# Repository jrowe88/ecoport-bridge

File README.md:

# EcoPort Bridge

EcoPort Bridge is a hobby reverse-engineering and hardware project to build a
communication bridge for appliances using the **CTA-2045 "EcoPort"** interface
(AC-form-factor UCM connector, RS-485 @ 19,200 baud) — starting with a
**Rinnai REHP65** heat pump water heater (CTA-2045-B / SGD, connector CN50,
physical connector part `420B2V12FL0`).

The goal is to expose the appliance's CTA-2045 data (tank temperature,
setpoint, operating state, energy, demand-response/shed status, faults, etc.)
to home automation systems (MQTT, Matter, Home Assistant) via a small
ESP32-class bridge device, built on top of a Python implementation of the
CTA-2045 protocol.

*Rev A: ESP32-C6 board with an on-board mains supply, plugged straight into
the heater's CTA-2045 connector. See [`hardware/rev-a`](hardware/rev-a) for
the board and [`hardware/enclosure`](hardware/enclosure) for the 3D-printed
case.*

## Design principles

- **Generic CTA-2045 core, separate from appliance-specific logic.** The
  `cta2045` layer implements the protocol (framing, messages, CRC, link,
  Basic DR / Intermediate messages). Appliance-specific behavior (e.g. Rinnai
  REHP65 quirks and capability mappings) lives under `appliances/rinnai` (or
  a Rinnai crate in firmware) so other CTA-2045/EcoPort appliances can be
  supported later without untangling Rinnai assumptions from the protocol
  implementation.
- **Protocol reverse engineering is kept separate from electrical reverse
  engineering.** Most of the protocol can be worked out via the EPRI UCM
  simulator without ever touching the heater.
- **Facts vs. hypotheses are recorded separately** in `docs/protocol.md` and
  per-capture notes, so reverse-engineering guesses don't quietly turn into
  "the spec" later.
- **Captures are first-class project artifacts.** Raw captures + notes live
  under `captures/` as a reproducible dataset, not a pile of Wireshark
  screenshots.

## Architecture

```text
                   ┌───────────────────────────────┐
                   │       Your application        │
                   │ Home Assistant / MQTT / etc.  │
                   └───────────────┬───────────────┘
                                   │
                         Python CTA-2045 API
                                   │
                   ┌───────────────▼───────────────┐
                   │       CTA-2045 protocol       │
                   │ link + Basic DR + Intermediate│
                   └───────────────┬───────────────┘
                                   │
                              RS-485 UART
                                   │
                   ┌───────────────▼───────────────┐
                   │       Isolated RS-485         │
                   │       transceiver             │
                   └───────────────┬───────────────┘
                                   │
                         CTA-2045 AC connector
                                   │
                   ┌───────────────▼───────────────┐
                   │       Rinnai REHP65           │
                   │          SGD / CN50           │
                   └───────────────────────────────┘
```

## Hardware notes (confirmed)

- Physical connector: `420B2V12FL0` (EPRI's "UCM Connector")
- Only pins **1 (D-), 7 (D+), 8 (GND)** are used; all other pins are left
  unconnected.
- EPRI documents 19,200 baud, 8 data bits, 1 stop bit, no parity.
- This is a mains-adjacent AC-form-factor interface — treat it with a
  deliberate electrical isolation strategy (isolated USB/RS-485 adapter).

See `docs/hardware.md` and `docs/protocol.md` for details, and `captures/`
for recorded traffic.

## Repository layout

```text
ecoport-bridge/
│
├── README.md
├── LICENSE             # AGPL-3.0 (software); hardware/LICENSE is CERN-OHL-S-2.0
├── CONTRIBUTING.md
│
├── docs/                 # architecture, hardware, protocol, HOWTOs
├── hardware/             # PCB revisions + 3D-printed enclosure
├── firmware/             # ESP32-C6 bridge firmware (Rust on ESP-IDF)
├── python/               # ecoport Python package (protocol + tooling)
├── tools/                # CLI tools: sniff, decode, query, interactive
├── captures/             # recorded protocol traffic + notes (EPRI + Rinnai)
├── test/                 # cross-cutting test fixtures/integration tests
└── scripts/              # dev setup / flashing helpers
```

## Status

Early planning / hardware on order. See `docs/reverse-engineering.md` and
`captures/` as the project progresses.

## Documentation

- [`docs/architecture.md`](docs/architecture.md) — software layering and the device ↔ Azure cloud architecture (telemetry, commands, storage, dashboard, security)
- [`docs/hardware.md`](docs/hardware.md) — connector, pinout, safety, bring-up hardware
- [`docs/protocol.md`](docs/protocol.md) — CTA-2045 protocol facts, capability matrix
- [`docs/capabilities.md`](docs/capabilities.md) — what we can see, infer, log and control on the Rinnai REHP65
- [`docs/reverse-engineering.md`](docs/reverse-engineering.md) — staged plan (EPRI oracle → passive capture → queries → writes)
- [`docs/references.md`](docs/references.md) — source material, tools, and libraries (EPRI, `python-cta2045`, ANSI, EcoPort DB, OpenADR, connector part numbers)
- [`docs/troubleshooting.md`](docs/troubleshooting.md) — common issues

## License

Both licenses are copyleft: you can use, modify and share this project, and
anything you distribute that's based on it has to stay under the same terms.

- **Software** (`firmware/`, `python/`, `tools/`, `scripts/`, `test/`) —
  GNU Affero General Public License v3.0 (`AGPL-3.0-only`), see
  [LICENSE](LICENSE).
- **Hardware** (`hardware/`: KiCad board, footprints, fab outputs, enclosure
  CAD) — CERN Open Hardware Licence v2, Strongly Reciprocal
  (`CERN-OHL-S-2.0`), see [hardware/LICENSE](hardware/LICENSE).
- **Docs and captures** — AGPL-3.0, same as the software.

Source location for the hardware (CERN-OHL-S §1.9):
<https://github.com/jrowe88/ecoport-bridge>. It is also printed on the board.

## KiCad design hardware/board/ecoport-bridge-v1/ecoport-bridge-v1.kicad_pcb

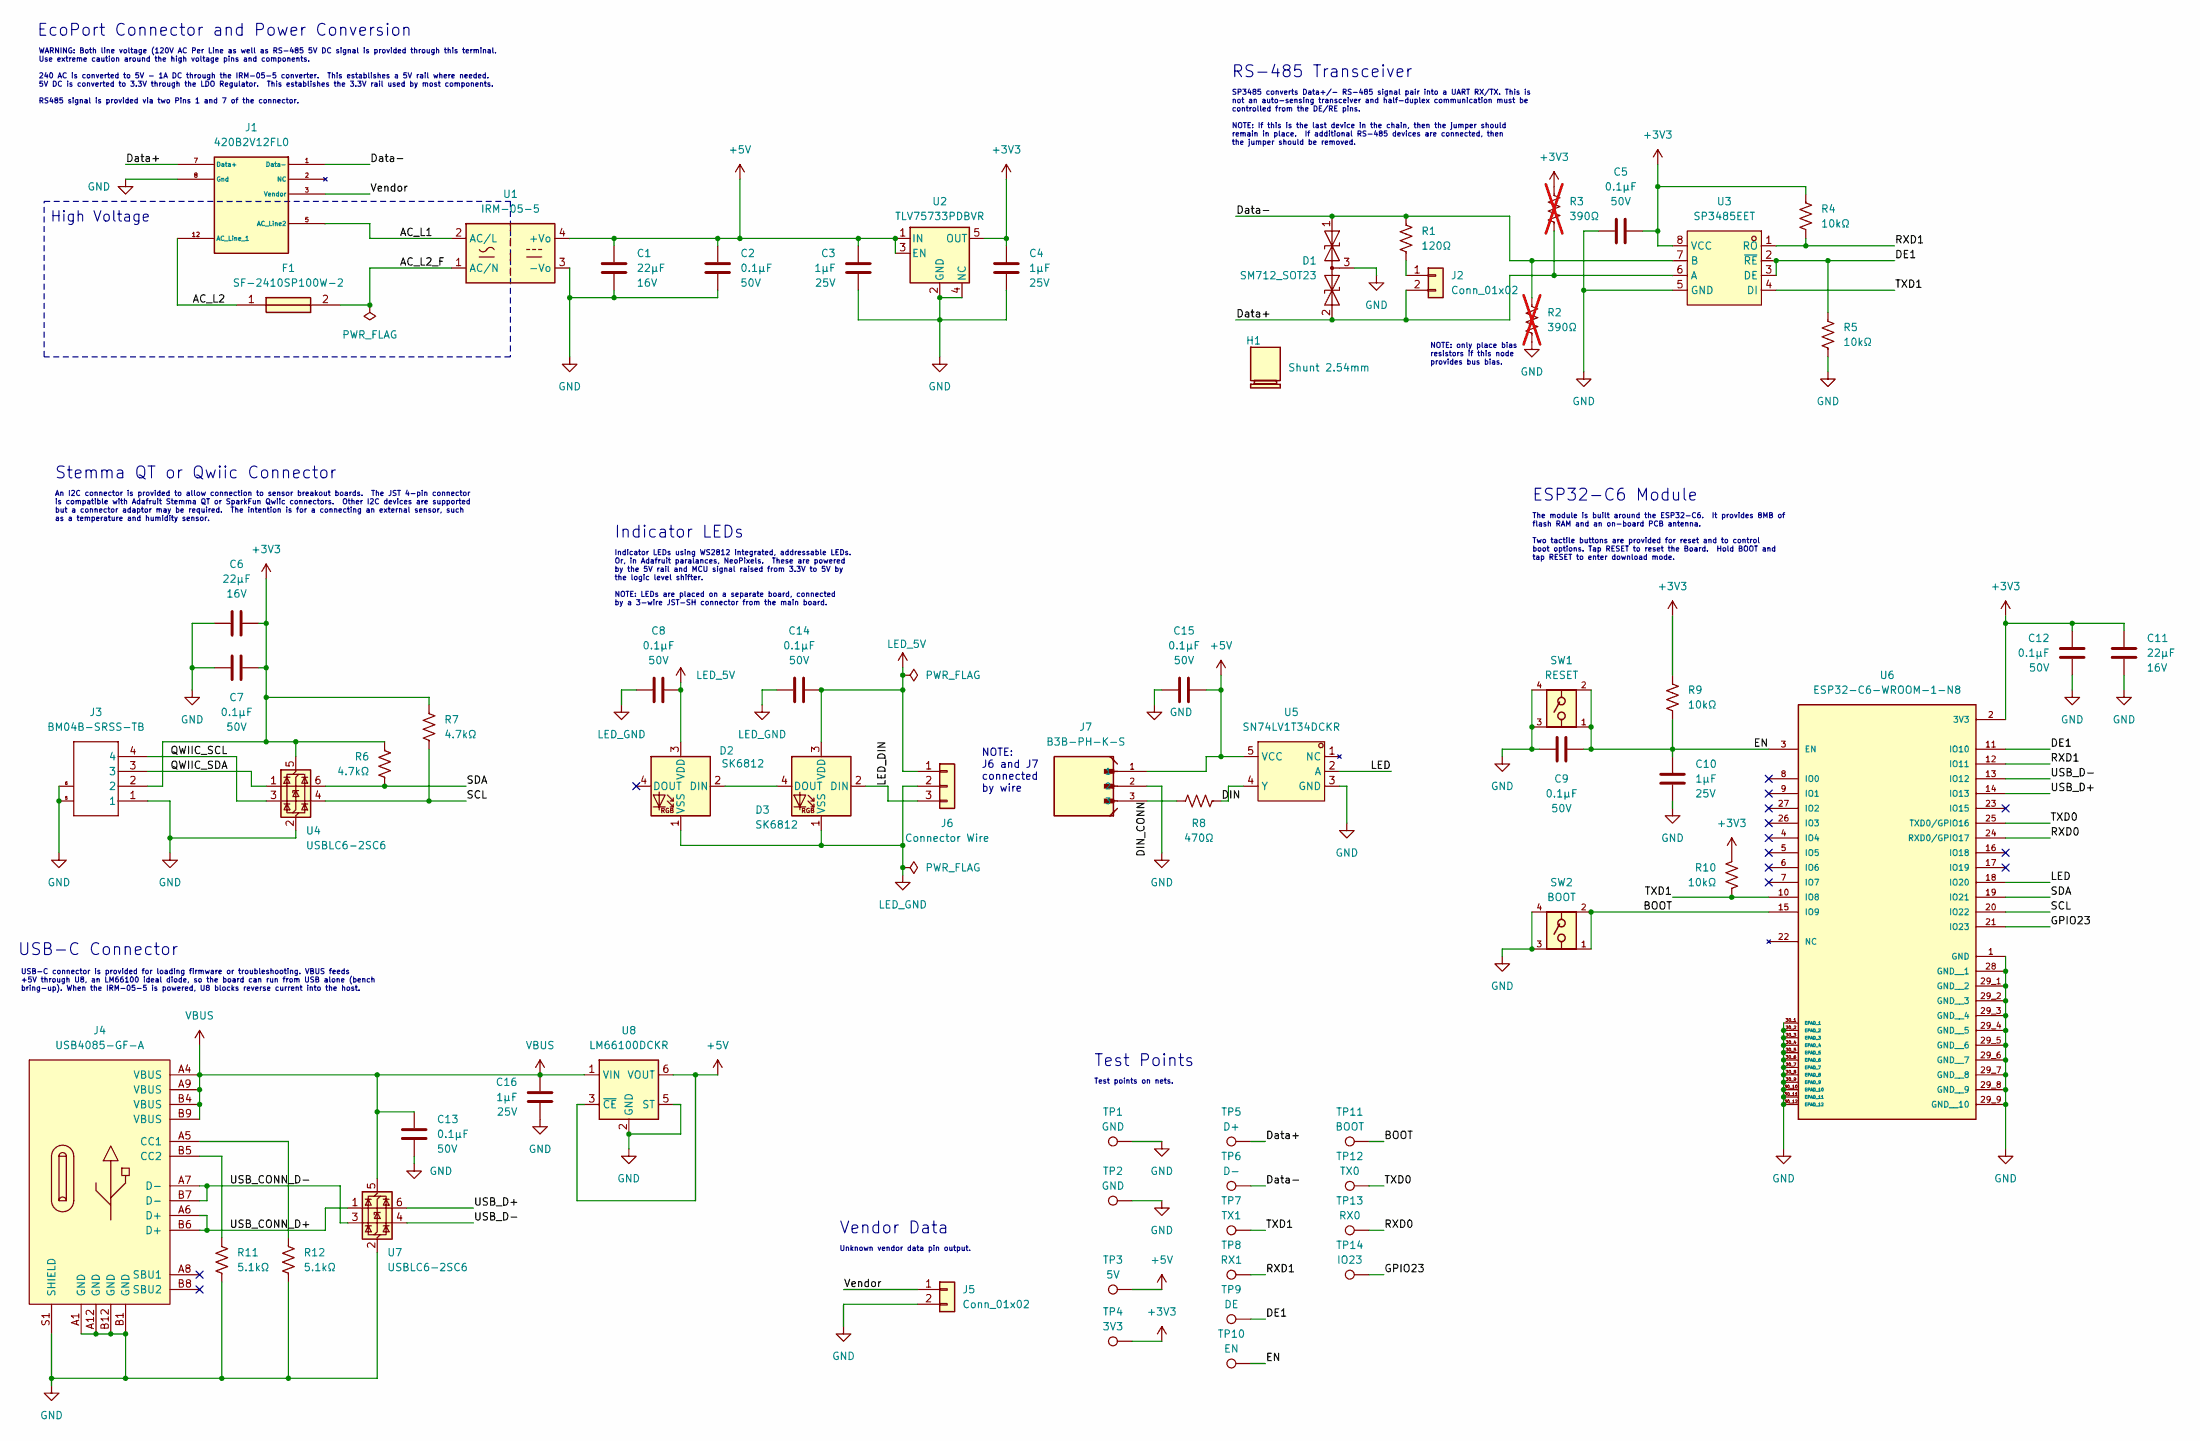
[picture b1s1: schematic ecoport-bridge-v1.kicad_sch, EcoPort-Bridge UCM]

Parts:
C1, C6, C11: 22µF; C_1206_3216Metric; Voltage 16V; MPN GRM319R61C226ME15J
C2, C5, C7, C8, C9, C12, C13, C14, C15: 0.1µF; C_0603_1608Metric; Voltage 50V; MPN GCJ188R71H104KA12D
C3, C4, C10, C16: 1µF; C_0603_1608Metric; Voltage 25V; MPN GRT188R71E105KE13D
D1: SM712_SOT23; SOT-23; MPN SM712
D2, D3: SK6812; LED_SK6812_PLCC4_5.0x5.0mm_P3.2mm; MPN SK6812
F1: SF-2410SP100W-2; FUSC6125X236N; Manufacturer_Part_Number SF-2410SP100W-2; Mouser Part Number 652-SF-2410SP100W-2
H1: Shunt 2.54mm; MPN QPC02SXGN-RC
J1: 420B2V12FL0; Onshore_Header_2x06_P4.20mm_Vertical; MPN 420B2V12FL0
J2, J5: Conn_01x02; PinHeader_1x02_P2.54mm_Vertical; MPN PREC002SAAN-RC
J3: BM04B-SRSS-TB; CONN4_BM04B-SRSS_JST; MPN BM04B-SRSS-TB(LF)(SN)
J4: USB4085-GF-A; USC-C-SMD_USB4085-GF-A; MPN USB4085-GF-A; LCSC Part C9900013983
J6: Connector Wire; Wire_Solder_1x03_P2.54mm_Relief
J7: B3B-PH-K-S; JST_B3B-PH-K-S; MPN B3B-PH-K-S(LF)(SN)
R1: 120Ω; R_1206_3216Metric; MPN RC1206FR-07120RL
R2, R3: 390Ω; R_0603_1608Metric; MPN RC0603FR-07390RL; not fitted
R4, R5, R9, R10: 10kΩ; R_0603_1608Metric; MPN RC0603FR-0710KL
R6, R7: 4.7kΩ; R_0603_1608Metric; MPN RC0603FR-074K7L
R8: 470Ω; R_0603_1608Metric; MPN RC0603FR-07470RL
R11, R12: 5.1kΩ; R_0603_1608Metric; MPN RC0603FR-075K1L
SW1: RESET; SW_TS04-66-50-BK-260-SMT; PARTREV 1.0
SW2: BOOT; SW_TS04-66-50-BK-260-SMT; PARTREV 1.0
TP1, TP2: GND; TestPoint_Keystone_5000-5004_Miniature; MPN 5001
TP3: 5V; TestPoint_Keystone_5000-5004_Miniature; MPN 5000
TP4: 3V3; TestPoint_Keystone_5000-5004_Miniature; MPN 5000
TP5: D+; TestPoint_Pad_D2.0mm
TP6: D-; TestPoint_Pad_D2.0mm
TP7: TX1; TestPoint_Pad_D2.0mm
TP8: RX1; TestPoint_Pad_D2.0mm
TP9: DE; TestPoint_Pad_D2.0mm
TP10: EN; TestPoint_Pad_D2.0mm
TP11: BOOT; TestPoint_Pad_D2.0mm
TP12: TX0; TestPoint_Pad_D2.0mm
TP13: RX0; TestPoint_Pad_D2.0mm
TP14: IO23; TestPoint_Keystone_5000-5004_Miniature; MPN 5000
U1: IRM-05-5; Converter_ACDC_MeanWell_IRM-05-xx_THT; MPN IRM-05-5
U2: TLV75733PDBVR; SOT-23-5; MPN TLV75733PDBVR
U3: SP3485EET; TSSOP-8_L4.4-W3.0-P0.65-LS6.4-BL; MPN SP3485EET; LCSC Part C20617894
U4, U7: USBLC6-2SC6; SOT-23-6; MPN USBLC6-2SC6
U5: SN74LV1T34DCKR; SC-70-5_L2.1-W1.3-P0.65-LS2.1-BR; MPN SN74LV1T34DCKR; LCSC Part C78541
U6: ESP32-C6-WROOM-1-N8; XCVR_ESP32-C6-WROOM-1-N8; PARTREV 1.0
U8: LM66100DCKR; SOT-363_SC-70-6; MPN LM66100DCKR

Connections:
+3V3: C4.1, C5.2, C6.2, C7.2, C11.2, C12.2, J3.2, R3.2, R4.2, R6.1, R7.1, R9.2, R10.2, TP4.1 (1_1), U2.5 (OUT), U3.8 (VCC), U4.5 (VBUS), U6.2 (3V3)
+5V: C1.1, C2.1, C3.1, C15.2, J7.1, TP3.1 (1_1), U1.4 (+Vo), U2.1 (IN), U2.3 (EN), U5.5 (VCC), U8.3 (~CE), U8.6 (VOUT)
/AC_L1: J1.5 (AC_Line2), U1.2 (AC/L)
/AC_L2: F1.1, J1.12 (AC_Line_1)
/AC_L2_F: F1.2, U1.1 (AC/N)
/BOOT: SW2.1, SW2.2, TP11.1 (1_1), U6.15 (IO9)
/DE1: R5.2, TP9.1 (1_1), U3.2 (~RE), U3.3 (DE), U6.11 (IO10)
/DIN: R8.1, U5.4 (Y)
/DIN_CONN: J7.3, R8.2
/Data+: D1.2 (A2), J1.7 (Data+), J2.2, R3.1, TP5.1 (1_1), U3.6 (A)
/Data-: D1.1 (A1), J1.1 (Data-), R1.1, R2.2, TP6.1 (1_1), U3.7 (B)
/EN: C9.2, C10.1, R9.1, SW1.1, SW1.2, TP10.1 (1_1), U6.3 (EN)
/GPIO23: TP14.1 (1_1), U6.21 (IO23)
/LED: U5.2 (A), U6.18 (IO20)
/LED_DIN: D3.2 (DIN), J6.3
/QWIIC_SCL: J3.4, U4.3 (I/O2)
/QWIIC_SDA: J3.3, U4.1 (I/O1)
/RXD0: TP13.1 (1_1), U6.24 (RXD0/GPIO17)
/RXD1: R4.1, TP8.1 (1_1), U3.1 (RO), U6.12 (IO11)
/SCL: R7.2, U4.4 (I/O2), U6.20 (IO22)
/SDA: R6.2, U4.6 (I/O1), U6.19 (IO21)
/TXD0: TP12.1 (1_1), U6.25 (TXD0/GPIO16)
/TXD1: R10.1, TP7.1 (1_1), U3.4 (DI), U6.10 (IO8)
/USB_CONN_D+: J4.A6 (D+), J4.B6 (D+), U7.1 (I/O1)
/USB_CONN_D-: J4.A7 (D-), J4.B7 (D-), U7.3 (I/O2)
/USB_D+: U6.14 (IO13), U7.6 (I/O1)
/USB_D-: U6.13 (IO12), U7.4 (I/O2)
/Vendor: J1.3 (Vendor), J5.1
GND: C1.2, C2.2, C3.2, C4.2, C5.1, C6.1, C7.1, C9.1, C10.2, C11.1, C12.1, C13.1, C15.1, C16.2, D1.3 (common), J1.8 (Gnd), J3.1, J3.5, J3.6, J4.A1 (GND), J4.A12 (GND), J4.B1 (GND), J4.B12 (GND), J4.S1 (SHIELD), J5.2, J7.2, R2.1, R5.1, R11.1, R12.1, SW1.3, SW1.4, SW2.3, SW2.4, TP1.1 (1_1), TP2.1 (1_1), U1.3 (-Vo), U2.2 (GND), U2.4 (NC), U3.5 (GND), U4.2 (GND), U5.3 (GND), U6.1 (GND), U6.28 (GND__1), U6.29_1 (GND__2), U6.29_2 (GND__3), U6.29_3 (GND__4), U6.29_4 (GND__5), U6.29_5 (GND__6), U6.29_6 (GND__7), U6.29_7 (GND__8), U6.29_8 (GND__9), U6.29_9 (GND__10), U6.30_1 (EPAD_1), U6.30_2 (EPAD_2), U6.30_3 (EPAD_3), U6.30_4 (EPAD_4), U6.30_5 (EPAD_5), U6.30_6 (EPAD_6), U6.30_7 (EPAD_7), U6.30_8 (EPAD_8), U6.30_9 (EPAD_9), U6.30_10 (EPAD_10), U6.30_11 (EPAD_11), U6.30_12 (EPAD_12), U7.2 (GND), U8.2 (GND), U8.5 (ST)
LED_5V: C8.2, C14.2, D2.3 (VDD), D3.3 (VDD), J6.1
LED_GND: C8.1, C14.1, D2.1 (VSS), D3.1 (VSS), J6.2
unnamed: D2.2 (DIN), D3.4 (DOUT)
unnamed: J2.1, R1.2
unnamed: J4.A5 (CC1), R12.2
unnamed: J4.B5 (CC2), R11.2
VBUS: C13.2, C16.1, J4.A4 (VBUS), J4.A9 (VBUS), J4.B4 (VBUS), J4.B9 (VBUS), U7.5 (VBUS), U8.1 (VIN)

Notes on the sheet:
Stemma QT or Qwiic Connector
Indicator LEDs
ESP32-C6 Module
WARNING: Both line voltage (120V AC Per Line as well as RS-485 5V DC signal is provided through this terminal. Use extreme caution around the high voltage pins and components. 240 AC is converted to 5V - 1A DC through the IRM-05-5 converter. This establishes a 5V rail where needed. 5V DC is convert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
NOTE: J6 and J7 connected by wire
EcoPort Connector and Power Conversion
High Voltage
An I2C connector is provided to allow connection to sensor breakout boards. The JST 4-pin connector is compatible with Adafruit Stemma QT or SparkFun Qwiic connectors. Other I2C devices are supported but a connector adaptor may be required. The intention is for a connecting an external sensor, such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
The module is built around the ESP32-C6. It provides 8MB of flash RAM and an on-board PCB antenna. Two tactile buttons are provided for reset and to control boot options. Tap RESET to reset the Board. Hold BOOT and tap RESET to enter download mode.
RS-485 Transceiver
Unknown vendor data pin output.
Test Points
USB-C Connector
SP3485 converts Data+/- RS-485 signal pair into a UART RX/TX. This is not an auto-sensing transceiver and half-duplex communication must be controlled from the DE/RE pins. NOTE: If this is the last device in the chain, then the jumper should remain in place. If additional RS-485 devices are connect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
NOTE: only place bias resistors if this node provides bus bias.
Vendor Data
Indicator LEDs using WS2812 integrated, addressable LEDs. Or, in Adafruit paralances, NeoPixels. These are powered by the 5V rail and MCU signal raised from 3.3V to 5V by the logic level shifter. NOTE: LEDs are placed on a separate board, connected by a 3-wire JST-SH connector from the main board.
USB-C connector is provided for loading firmware or troubleshooting. VBUS feeds +5V through U8, an LM66100 ideal diode, so the board can run from USB alone (bench bring-up). When the IRM-05-5 is powered, U8 blocks reverse current into the host.
Test points on nets.

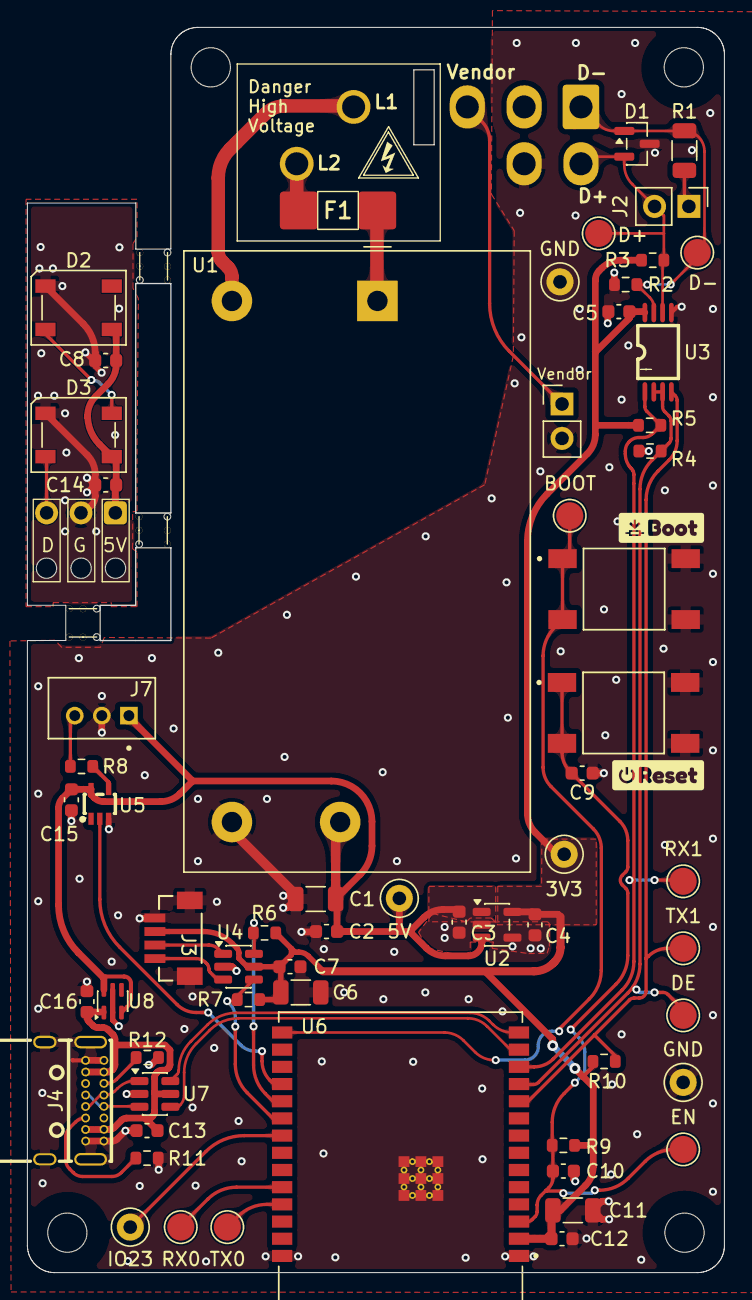
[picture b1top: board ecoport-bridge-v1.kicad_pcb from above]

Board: 2 copper layers, 51.5 x 92.0 mm, 65 parts (1 on the bottom side), 36 nets.

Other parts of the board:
kobee-studio-6AD3D2C7: Kobee Studio; kobee-studio-6AD3D2C7
kobee-studio-6AD3E735: Kobee Studio; kobee-studio-6AD3E735

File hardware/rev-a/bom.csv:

Reference,Description,Manufacturer,MPN,Quantity,DigiKey,Notes
"C1,C6,C11",Cap 22uF 16V X5R 1206,Murata Electronics,GRM319R61C226ME15J,3,490-GRM319R61C226ME15JCT-ND,
"C2,C5,C7,C8,C9,C12-C15",Cap 0.1uF 50V X7R 0603,Murata Electronics,GCJ188R71H104KA12D,9,490-5798-1-ND,
"C3,C4,C10,C16",Cap 1uF 25V X7R 0603,Murata Electronics,GRT188R71E105KE13D,4,490-GRT188R71E105KE13DCT-ND,
D1,TVS RS-485 SM712 SOT-23,SMC Diode Solutions,SM712,1,1655-SM712CT-ND,
"D2,D3",SK6812 addressable LED 5050 PLCC4 (LED strip),OPSCO Optoelectronics,SK6812,2,,Not stocked bare at DigiKey; use own stock or LCSC/Adafruit
F1,Fuse 1A 250VAC time-lag 2410,Bourns,SF-2410SP100W-2,1,SF-2410SP100W-2CT-ND,Marking letter E
H1,Jumper shunt 2.54mm,Sullins Connector Solutions,QPC02SXGN-RC,1,S9337-ND,Termination jumper on J2
J1,CTA-2045 header 2x6 4.2mm vertical,On Shore Technology Inc.,420B2V12FL0,1,52-420B2V12FL0-ND,"Pull pins 4, 6, 9, 10, 11 before soldering"
"J2,J5",Header 1x2 2.54mm,Sullins Connector Solutions,PREC002SAAN-RC,2,35-PREC002SAAN-RC-ND,
J3,JST SH 4-pin top-entry (Qwiic),JST Sales America Inc.,BM04B-SRSS-TB(LF)(SN),1,455-BM04B-SRSS-TBCT-ND,
J4,USB-C receptacle USB2.0,GCT,USB4085-GF-A,1,2073-USB4085-GF-ACT-ND,
J7,JST PH 3-pin header (LED strip),JST Sales America Inc.,B3B-PH-K-S(LF)(SN),1,455-1705-ND,
J7 mate housing,JST PH 3-pin housing (LED cable),JST Sales America Inc.,PHR-3,1,455-1126-ND,Not on schematic: mates with J7
J7 mate crimps,JST PH crimp socket 24-30AWG,JST,SPH-002T-P0.5S,3,,Not on schematic: 3 per cable; order by MPN (several DigiKey packagings)
R1,Res 120R 1% 1206,YAGEO,RC1206FR-07120RL,1,311-120FRCT-ND,RS-485 termination
"R6,R7",Res 4.7k 1% 0603,YAGEO,RC0603FR-074K7L,2,311-4.70KHRCT-ND,
R8,Res 470R 1% 0603,YAGEO,RC0603FR-07470RL,1,311-470HRCT-ND,
"R4,R5,R9,R10",Res 10k 1% 0603,Vishay Dale,CRCW060310K0FKEA,4,541-10.0KHCT-ND,Sub for YAGEO RC0603FR-0710KL (0 stock at DigiKey)
"R11,R12",Res 5.1k 1% 0603,Vishay Dale,CRCW06035K10FKEA,2,541-5.10KHCT-ND,Sub for YAGEO RC0603FR-075K1L (0 stock at DigiKey). USB-C CC pull-downs
"SW1,SW2","Tactile switch SMD (RESET, BOOT)",Same Sky (Formerly CUI Devices),TS04-66-50-BK-260-SMT,2,2223-TS04-66-50-BK-260-SMT-ND,
U1,AC-DC 5V 1A IRM-05-5,MEAN WELL USA Inc.,IRM-05-5,1,1866-3027-ND,
U2,LDO 3.3V 1A SOT-23-5,Texas Instruments,TLV75733PDBVR,1,296-50414-1-ND,0 stock at DigiKey. TLV75733PDYDR (thin SOT-23-5) is in stock; verify pinout/footprint before substituting
U3,RS-485 transceiver SP3485 TSSOP-8,UMW,SP3485EET,1,4518-SP3485EETCT-ND,
"U4,U7",USB ESD USBLC6-2SC6,STMicroelectronics,USBLC6-2SC6,2,497-5235-1-ND,
U5,Level shifter SN74LV1T34 SC-70-5,Texas Instruments,SN74LV1T34DCKR,1,296-37177-1-ND,
U6,ESP32-C6-WROOM-1-N8 module,Espressif Systems,ESP32-C6-WROOM-1-N8,1,1965-ESP32-C6-WROOM-1-N8CT-ND,
U8,Ideal diode LM66100 SC-70-6,Texas Instruments,LM66100DCKR,1,296-53541-1-ND,USB VBUS to +5V
"TP1,TP2",Test point miniature black,Keystone Electronics,5001,2,36-5001-ND,GND
"TP3,TP4,TP14",Test point miniature red,Keystone Electronics,5000,3,36-5000-ND,TP14 is marked not-in-BOM in the schematic; included here because it uses the Keystone footprint
"R2,R3",Res 390R 1% 0603 (bus bias),YAGEO,RC0603FR-07390RL,0,,DNP unless this node biases the bus
--,M2.5 screws for case (4 per board),,,4,,"Use nylon at the hole by J1/AC_L1 (64.05, 35.15); see mounting-hole note"

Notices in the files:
parts and their libraries:
JROWE DESIGNS  CERN-OHL-S-2.0
